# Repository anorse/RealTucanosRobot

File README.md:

# RealTucanosRobot
Senior Project CAD files

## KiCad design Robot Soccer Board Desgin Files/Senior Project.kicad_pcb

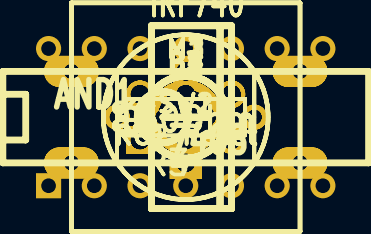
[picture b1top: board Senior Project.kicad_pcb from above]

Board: 2 copper layers, 16 parts (0 on the bottom side), 5 nets, no tracks yet.

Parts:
AND1: 7408; DIP-14__300
B1, B2, B3, B4: PWR; 1pin
M1: M1; pin_array_3x2
M2: M2; pin_array_3x2
M3: M3; pin_array_3x2
Q1, Q2: IRF740; TO220_VERT
R1, R2: 150Ohm; R3
R3, R4: 470 Ohm; R1
SW1: RC2 Reset; SW_PUSH-12mm
SW2: RC1 Reset; SW_PUSH-12mm

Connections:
5V: AND1.14, R3.2, R4.2
GND: AND1.7, B1.1, R1.2, R2.2, SW1.2, SW2.2
unnamed: B2.1, B3.1
unnamed: Q2.2, R4.1, SW2.1
unnamed: Q1.2, R3.1, SW1.1

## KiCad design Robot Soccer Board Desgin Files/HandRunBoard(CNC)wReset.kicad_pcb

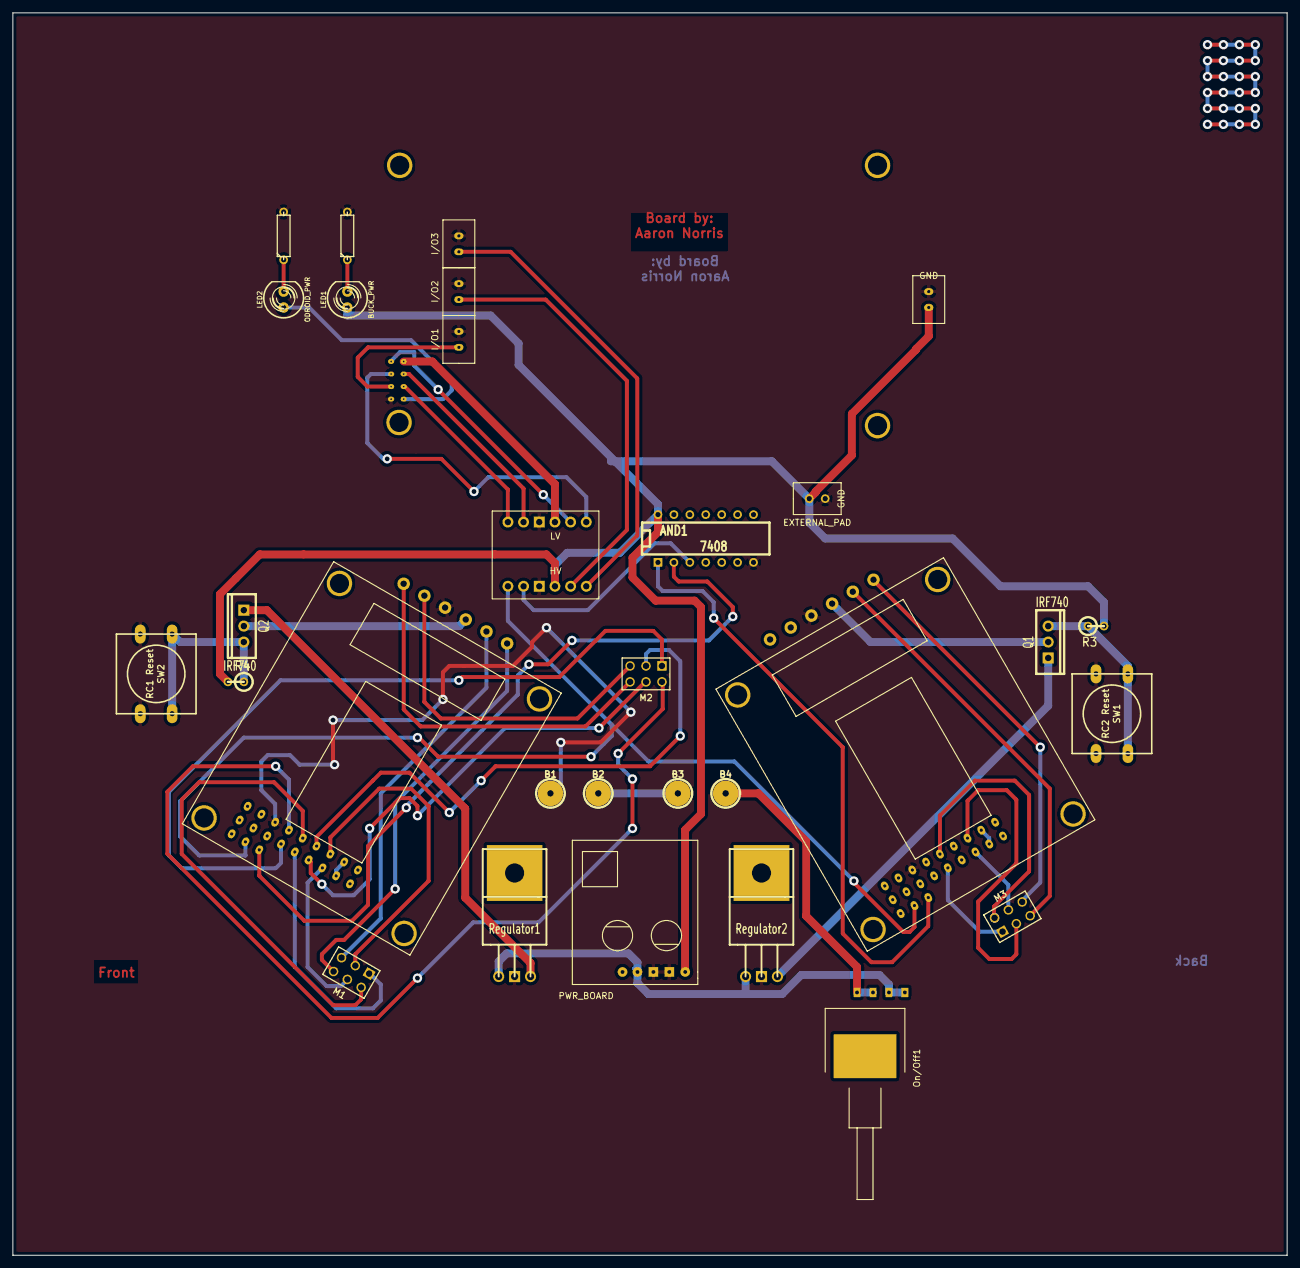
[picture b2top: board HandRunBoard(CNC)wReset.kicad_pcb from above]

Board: 2 copper layers, 203.2 x 198.1 mm, 31 parts (1 on the bottom side), 46 nets.

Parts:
5v1, 5v2: EXTERNAL_PAD; IO_Foot_Dual
AND1: 7408; DIP-14__300
B1, B2, B3, B4: PWR; 1pin
I/O1: PAD; IO_Foot_Dual
I/O2, I/O3: EXTERNAL_PAD; IO_Foot_Dual
LED1: BUCK_PWR; LED5MM
LED2: ODROID_PWR; LED5MM
LLC1: LOGIC_LEVEL_CONVERTER; Logic_lvl_SparkFun
M1: M1; pin_array_3x2
M2: M2; pin_array_3x2
M3: M3; pin_array_3x2
ODROID1: ODROID; ODROID_v3
On/Off1: SPST; Power_Switch_Custom
PB1: PWR_BOARD; PowerBoard
Q1, Q2: IRF740; TO220_VERT
R1, R2: 150Ohm; R3
R3, R4: 470 Ohm; R1
RC1, RC2: ROBOCLAW; ROBOCLAW_V2
Regulator1, Regulator2: V_REG_78XXTO-92; Custom_LM7812
SW1: RC2 Reset; SW_PUSH-12mm
SW2: RC1 Reset; SW_PUSH-12mm

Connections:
5V: 5v1.1, 5v2.1, AND1.14, LED1.1, LLC1.3, PB1.1, R3.2, R4.2
12V(1): Q2.1, Regulator1.3
12V(2): Q1.1, Regulator2.3
GND: 5v1.2, 5v2.2, AND1.7, B1.1, I/O1.2, I/O2.2, I/O3.2, LLC1.4, LLC1.10, ODROID1.7, PB1.2, PB1.3, R1.2, R2.2, RC1.9, RC1.24, RC2.9, RC2.24, Regulator1.1, Regulator2.1, SW1.2, SW2.2
unnamed: M1.6, RC1.27
unnamed: M2.5, RC1.23
unnamed: M2.6, RC1.22
unnamed: M3.5, RC2.26
unnamed: M3.6, RC2.27
unnamed: M1.4, RC1.16
unnamed: M1.3, RC1.17
unnamed: LED1.2, R1.1
unnamed: M2.4, RC1.14
unnamed: AND1.3, LLC1.5
unnamed: M1.5, RC1.26
unnamed: M2.2, RC1.11
unnamed: M2.1, RC1.10
unnamed: M3.2, RC2.13
unnamed: M3.1, RC2.12
unnamed: M2.3, RC1.15
unnamed: M3.3, RC2.17
unnamed: M3.4, RC2.16
unnamed: M1.2, RC1.13
unnamed: M1.1, RC1.12
unnamed: B4.1, On/Off1.1
unnamed: B2.1, B3.1
unnamed: Q2.2, R4.1, SW2.1
unnamed: Q1.2, R3.1, SW1.1
unnamed: LLC1.12, ODROID1.6
unnamed: LLC1.11, ODROID1.4
unnamed: LLC1.9, ODROID1.2
unnamed: LLC1.8, ODROID1.1
unnamed: LLC1.7, ODROID1.3
unnamed: LED2.1, ODROID1.8
unnamed: LED2.2, R2.1
unnamed: I/O3.1, LLC1.1
unnamed: On/Off1.2, PB1.4, Regulator1.2, Regulator2.2
unnamed: I/O2.1, LLC1.2
unnamed: I/O1.1, ODROID1.5
unnamed: RC2.18, RC2.19
unnamed: RC1.18, RC1.19
unnamed: AND1.2, RC1.7
unnamed: LLC1.6, RC1.4, RC2.4
unnamed: AND1.1, RC2.7
RCin(1): Q2.3, RC1.25
RCin(2): Q1.3, RC2.25

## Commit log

2015-08-06 All the design files I needed to have my CNC'd senior project
